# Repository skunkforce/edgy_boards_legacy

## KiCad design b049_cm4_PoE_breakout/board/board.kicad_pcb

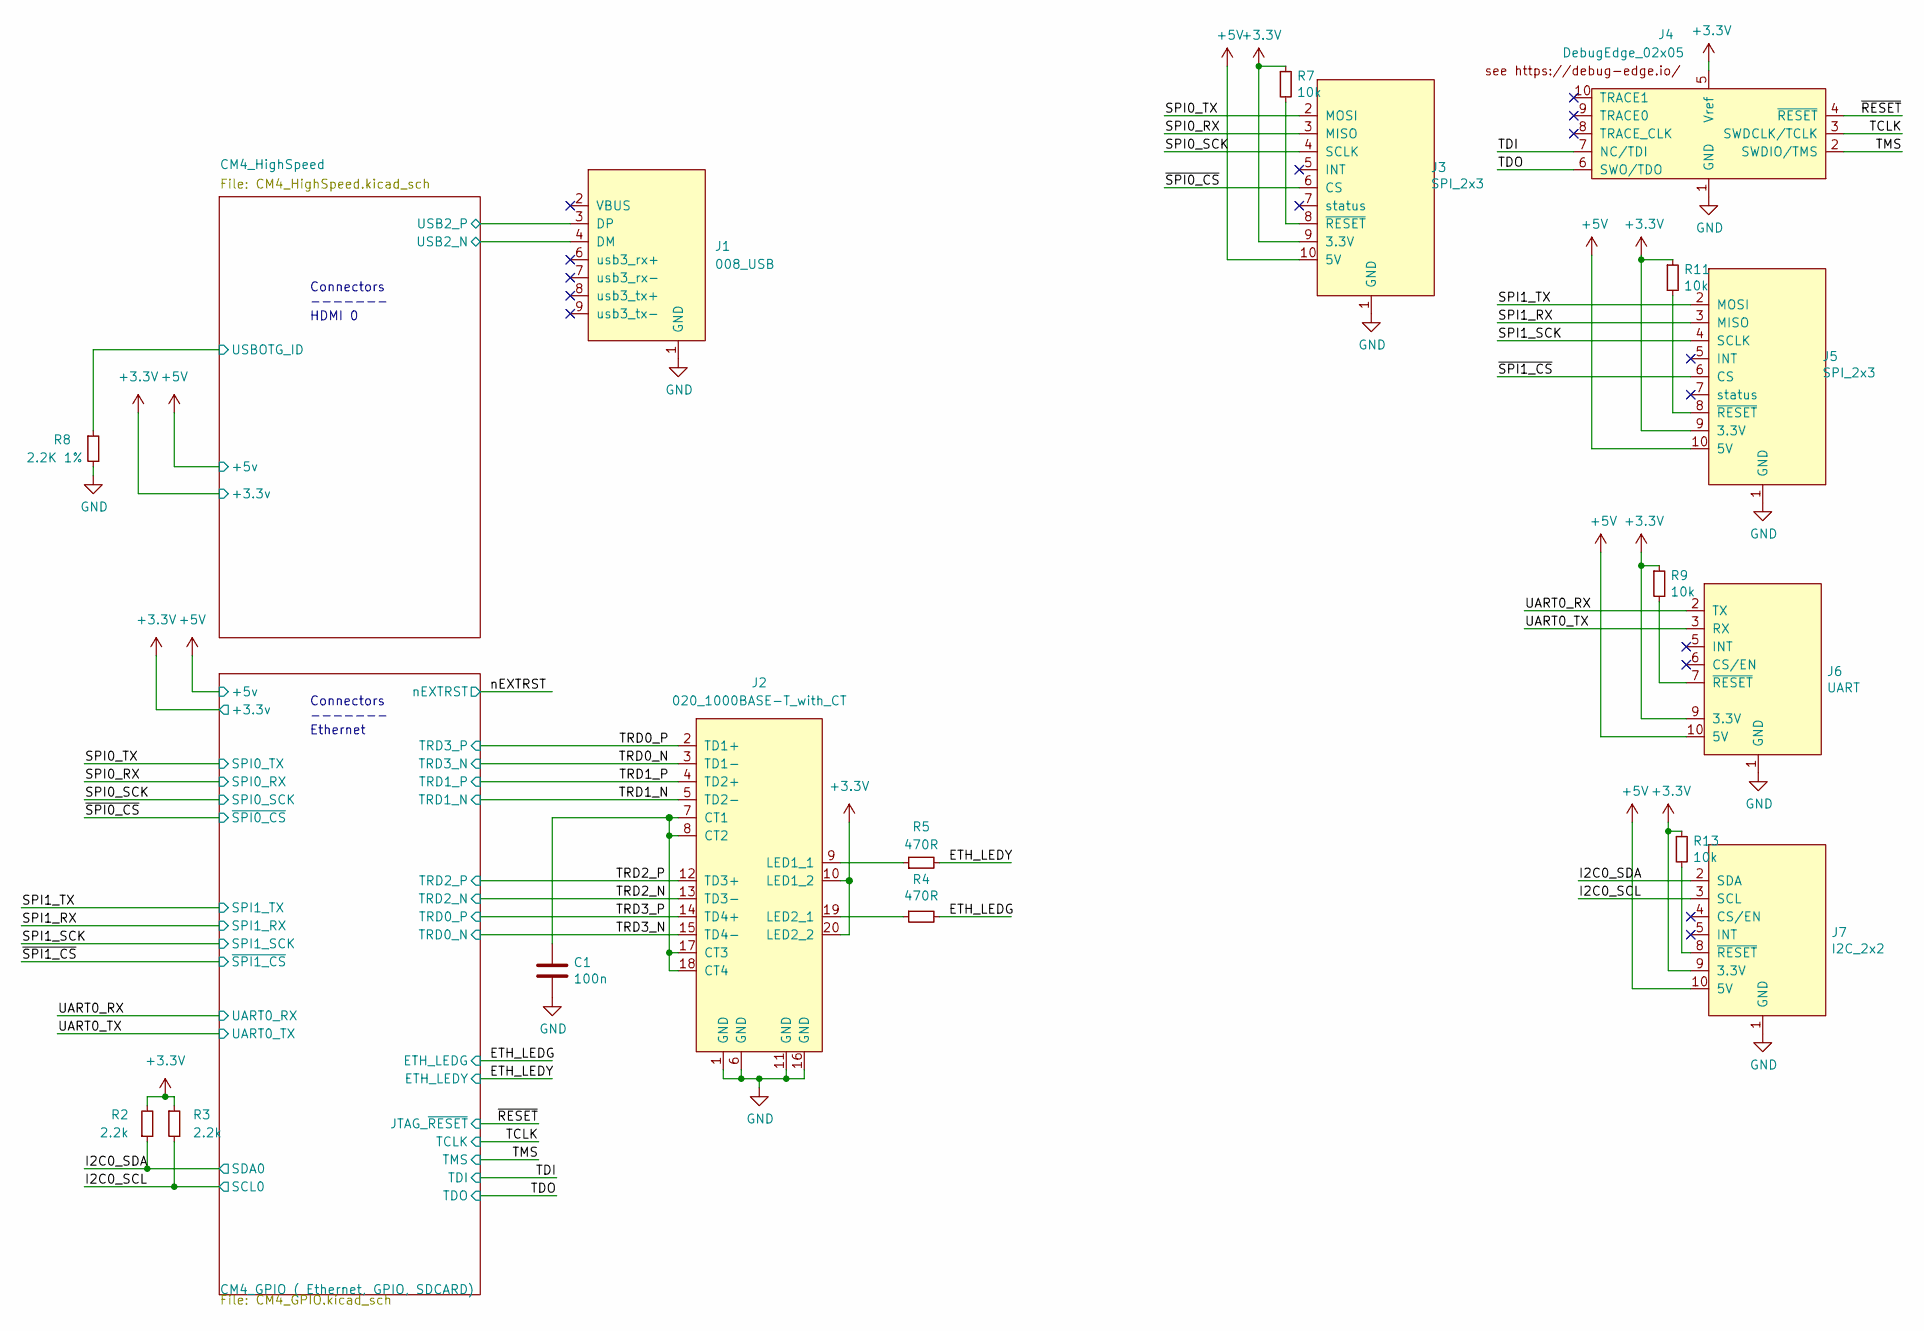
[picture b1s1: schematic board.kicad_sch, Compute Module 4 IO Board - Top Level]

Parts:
C1: 100n; C_0402_1005Metric; Part Description 0.1uF 10% 16V Ceramic Capacitor X7R 040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
J1: 008_USB; on_edge_2x05_host
J2: 020_1000BASE-T_with_CT; on_edge_2x10_host
J3: SPI_2x3; on_edge_2x05_up_host
J4: DebugEdge_02x05; debug_edge_2x05_host
J5: SPI_2x3; on_edge_2x05_host
J6: UART; on_edge_2x05_host
J7: I2C_2x2; on_edge_2x05_host
R2, R3: 2.2k; R_0603_1608Metric
R4, R5: 470R; R_0402_1005Metric; Part Description Resistor 470R M1005 1% 63mW
R7, R9, R11, R13: 10k; R_0603_1608Metric
R8: 2.2K 1%; R_0402_1005Metric; Part Description Resistor 2.2K M1005 1% 63mW

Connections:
+3V3: J2.10 (LED1_2), J2.20 (LED2_2), J3.9 (3.3V), J4.5 (Vref), J5.9 (3.3V), J6.9 (3.3V), J7.9 (3.3V), R2.2, R3.1, R7.1, R9.1, R11.1, R13.1; also elsewhere on the board
+5V: J3.10 (5V), J5.10 (5V), J6.10 (5V), J7.10 (5V); also elsewhere on the board
/CM4_HighSpeed/USB2_N: J1.4 (DM); also elsewhere on the board
/CM4_HighSpeed/USB2_P: J1.3 (DP); also elsewhere on the board
/CM4_HighSpeed/USBOTG_ID: R8.1; also elsewhere on the board
/ETH_LEDG: R4.2; also elsewhere on the board
/ETH_LEDY: R5.2; also elsewhere on the board
/I2C0_SCL: J7.3 (SCL), R3.2; also elsewhere on the board
/I2C0_SDA: J7.2 (SDA), R2.1; also elsewhere on the board
/SPI0_RX: J3.3 (MISO); also elsewhere on the board
/SPI0_SCK: J3.4 (SCLK); also elsewhere on the board
/SPI0_TX: J3.2 (MOSI); also elsewhere on the board
/SPI1_RX: J5.3 (MISO); also elsewhere on the board
/SPI1_SCK: J5.4 (SCLK); also elsewhere on the board
/SPI1_TX: J5.2 (MOSI); also elsewhere on the board
/TCLK: J4.3 (SWDCLK/TCLK); also elsewhere on the board
/TDI: J4.7 (NC/TDI); also elsewhere on the board
/TDO: J4.6 (SWO/TDO); also elsewhere on the board
/TMS: J4.2 (SWDIO/TMS); also elsewhere on the board
/TRD0_N: J2.3 (TD1-); also elsewhere on the board
/TRD0_P: J2.2 (TD1+); also elsewhere on the board
/TRD1_N: J2.5 (TD2-); also elsewhere on the board
/TRD1_P: J2.4 (TD2+); also elsewhere on the board
/TRD2_N: J2.13 (TD3-); also elsewhere on the board
/TRD2_P: J2.12 (TD3+); also elsewhere on the board
/TRD3_N: J2.15 (TD4-); also elsewhere on the board
/TRD3_P: J2.14 (TD4+); also elsewhere on the board
/UART0_RX: J6.2 (TX); also elsewhere on the board
/UART0_TX: J6.3 (RX); also elsewhere on the board
/~RESET: J4.4 (~RESET); also elsewhere on the board
/~SPI0_CS: J3.6 (CS); also elsewhere on the board
/~SPI1_CS: J5.6 (CS); also elsewhere on the board
GND: C1.2, J1.1 (GND), J2.1 (GND), J2.6 (GND), J2.11 (GND), J2.16 (GND), J3.1 (GND), J4.1 (GND), J5.1 (GND), J6.1 (GND), J7.1 (GND), R8.2; also elsewhere on the board
unnamed: C1.1, J2.7 (CT1), J2.8 (CT2), J2.17 (CT3), J2.18 (CT4)
unnamed: J2.9 (LED1_1), R5.1
unnamed: J2.19 (LED2_1), R4.1
unnamed: J3.8 (~RESET), R7.2
unnamed: J5.8 (~RESET), R11.2
unnamed: J6.7 (~RESET), R9.2
unnamed: J7.8 (~RESET), R13.2

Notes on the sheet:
Connectors ------- Ethernet
Connectors ------- HDMI 0

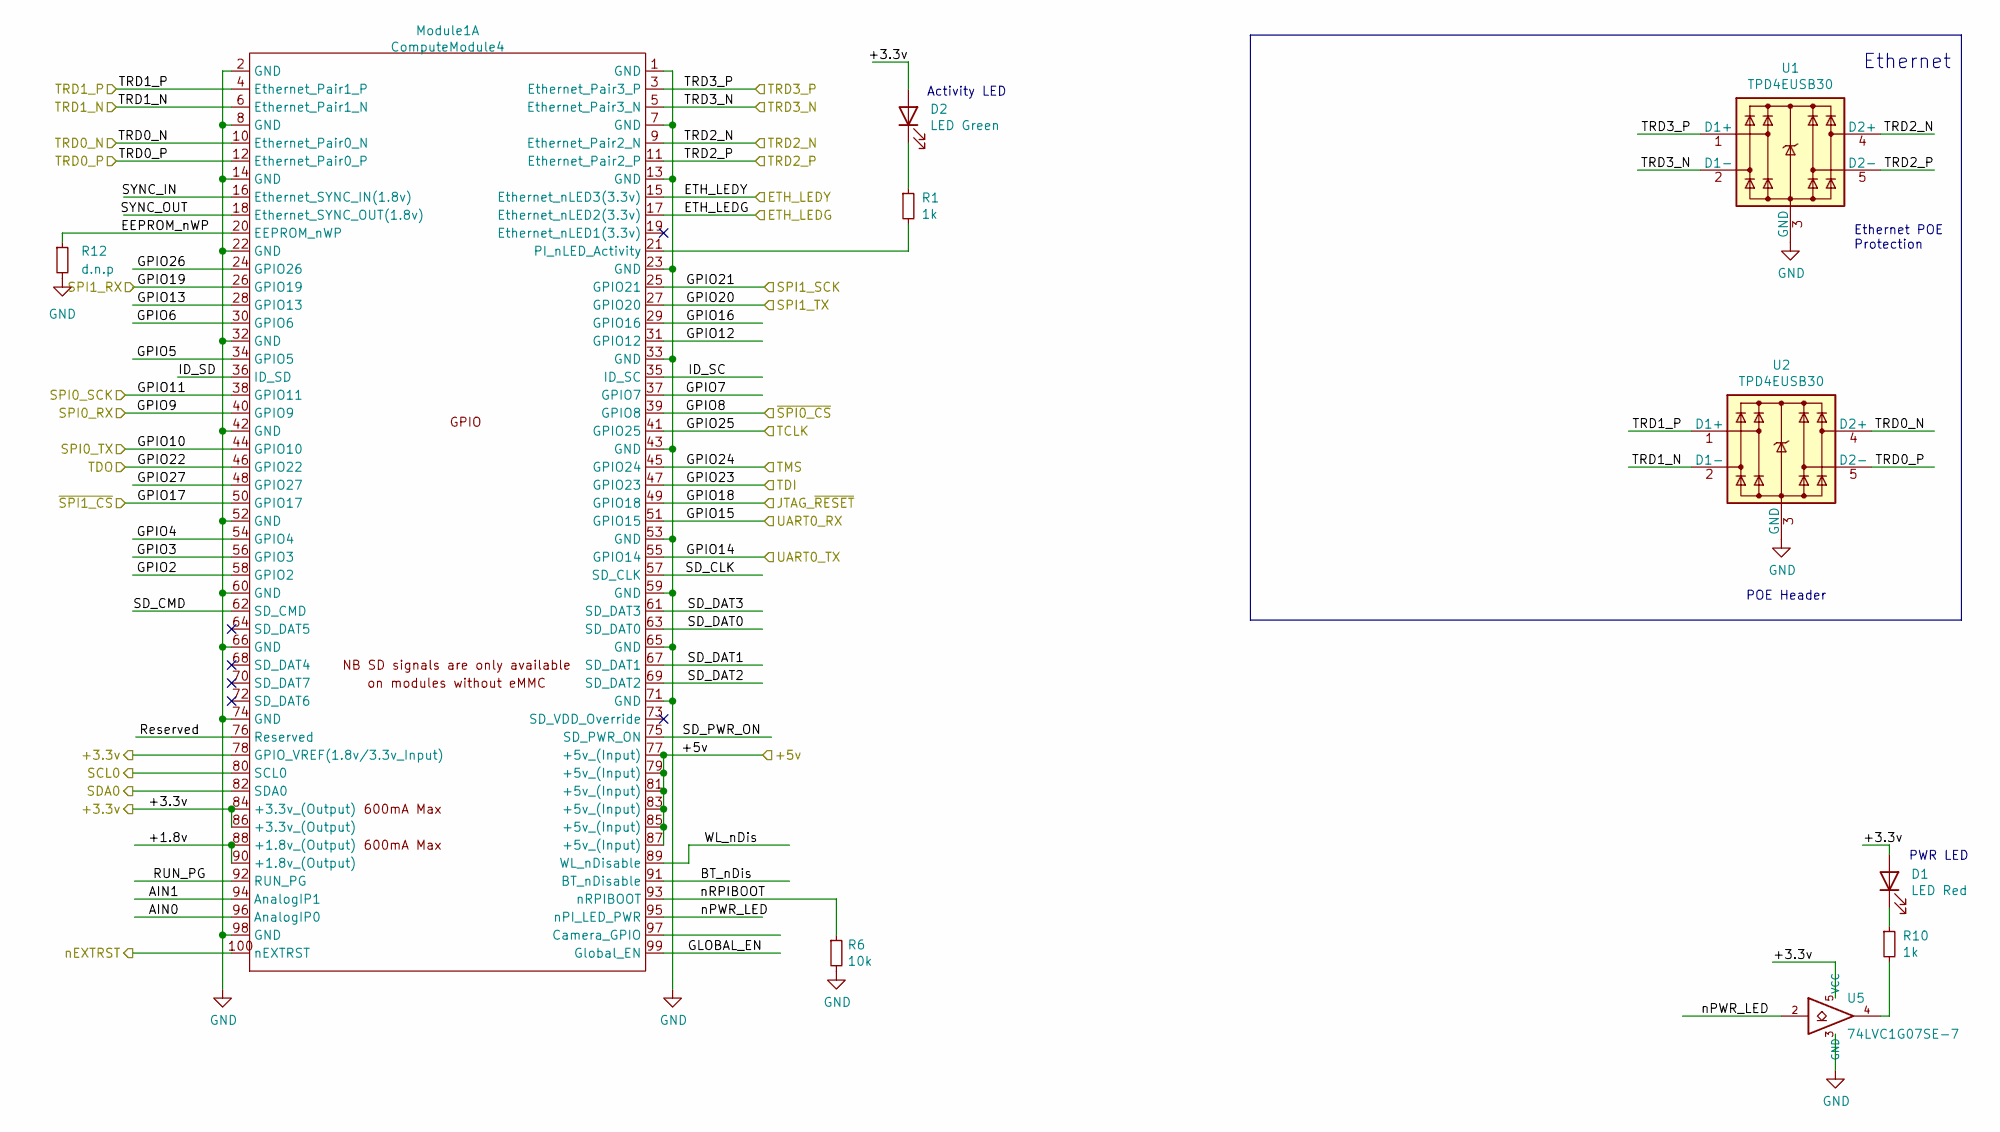
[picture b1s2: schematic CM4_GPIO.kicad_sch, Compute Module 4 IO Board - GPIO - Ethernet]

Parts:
D1: LED Red; LED_0603_1608Metric; Part Description Red 620nm LED Indication - Discrete 2.2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
D2: LED Green; LED_0603_1608Metric; Part Description Green 572nm LED Indication - Discrete 2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
Module1: ComputeModule4; Raspberry-Pi-4-Compute-Module; Part Description 100 Position Connector Receptacle, Cent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
R1, R10: 1k; R_0402_1005Metric; Part Description Resistor 1K M1005 1% 63mW
R6: 10k; R_0603_1608Metric
R12: d.n.p; R_0603_1608Metric
U1, U2: TPD4EUSB30; USON-10_2.5x1.0mm_P0.5mm; Part Description Quad TVS diode for high speed signals (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
U5: 74LVC1G07SE-7; SOT-353_SC-70-5; Part Description Buffer, Non-Inverting 1 Element 1 Bit p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

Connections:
+3V3: D1.2 (A), D2.2 (A), Module1.78 (GPIO_VREF(1.8v/3.3v_Input)), Module1.84 (+3.3v_(Output)), Module1.86 (+3.3v_(Output)), U5.5 (VCC); also elsewhere on the board
+5V: Module1.77 (+5v_(Input)), Module1.79 (+5v_(Input)), Module1.81 (+5v_(Input)), Module1.83 (+5v_(Input)), Module1.85 (+5v_(Input)), Module1.87 (+5v_(Input)); also elsewhere on the board
/CM4_GPIO ( Ethernet, GPIO, SDCARD)/+1.8v: Module1.88 (+1.8v_(Output)), Module1.90 (+1.8v_(Output))
/CM4_GPIO ( Ethernet, GPIO, SDCARD)/AIN0: Module1.96 (AnalogIP0)
/CM4_GPIO ( Ethernet, GPIO, SDCARD)/AIN1: Module1.94 (AnalogIP1)
/CM4_GPIO ( Ethernet, GPIO, SDCARD)/BT_nDis: Module1.91 (BT_nDisable)
/CM4_GPIO ( Ethernet, GPIO, SDCARD)/EEPROM_nWP: Module1.20 (EEPROM_nWP), R12.1
/CM4_GPIO ( Ethernet, GPIO, SDCARD)/GLOBAL_EN: Module1.99 (Global_EN)
/CM4_GPIO ( Ethernet, GPIO, SDCARD)/GPIO2: Module1.58 (GPIO2)
/CM4_GPIO ( Ethernet, GPIO, SDCARD)/GPIO3: Module1.56 (GPIO3)
/CM4_GPIO ( Ethernet, GPIO, SDCARD)/GPIO4: Module1.54 (GPIO4)
/CM4_GPIO ( Ethernet, GPIO, SDCARD)/GPIO5: Module1.34 (GPIO5)
/CM4_GPIO ( Ethernet, GPIO, SDCARD)/GPIO6: Module1.30 (GPIO6)
/CM4_GPIO ( Ethernet, GPIO, SDCARD)/GPIO7: Module1.37 (GPIO7)
/CM4_GPIO ( Ethernet, GPIO, SDCARD)/GPIO12: Module1.31 (GPIO12)
/CM4_GPIO ( Ethernet, GPIO, SDCARD)/GPIO13: Module1.28 (GPIO13)
/CM4_GPIO ( Ethernet, GPIO, SDCARD)/GPIO16: Module1.29 (GPIO16)
/CM4_GPIO ( Ethernet, GPIO, SDCARD)/GPIO26: Module1.24 (GPIO26)
/CM4_GPIO ( Ethernet, GPIO, SDCARD)/GPIO27: Module1.48 (GPIO27)
/CM4_GPIO ( Ethernet, GPIO, SDCARD)/ID_SC: Module1.35 (ID_SC)
/CM4_GPIO ( Ethernet, GPIO, SDCARD)/ID_SD: Module1.36 (ID_SD)
/CM4_GPIO ( Ethernet, GPIO, SDCARD)/RUN_PG: Module1.92 (RUN_PG)
/CM4_GPIO ( Ethernet, GPIO, SDCARD)/Reserved: Module1.76 (Reserved)
/CM4_GPIO ( Ethernet, GPIO, SDCARD)/SD_CLK: Module1.57 (SD_CLK)
/CM4_GPIO ( Ethernet, GPIO, SDCARD)/SD_CMD: Module1.62 (SD_CMD)
/CM4_GPIO ( Ethernet, GPIO, SDCARD)/SD_DAT0: Module1.63 (SD_DAT0)
/CM4_GPIO ( Ethernet, GPIO, SDCARD)/SD_DAT1: Module1.67 (SD_DAT1)
/CM4_GPIO ( Ethernet, GPIO, SDCARD)/SD_DAT2: Module1.69 (SD_DAT2)
/CM4_GPIO ( Ethernet, GPIO, SDCARD)/SD_DAT3: Module1.61 (SD_DAT3)
/CM4_GPIO ( Ethernet, GPIO, SDCARD)/SD_PWR_ON: Module1.75 (SD_PWR_ON)
/CM4_GPIO ( Ethernet, GPIO, SDCARD)/SYNC_IN: Module1.16 (Ethernet_SYNC_IN(1.8v))
/CM4_GPIO ( Ethernet, GPIO, SDCARD)/SYNC_OUT: Module1.18 (Ethernet_SYNC_OUT(1.8v))
/CM4_GPIO ( Ethernet, GPIO, SDCARD)/WL_nDis: Module1.89 (WL_nDisable)
/CM4_GPIO ( Ethernet, GPIO, SDCARD)/nPWR_LED: Module1.95 (nPI_LED_PWR), U5.2
/CM4_GPIO ( Ethernet, GPIO, SDCARD)/nRPIBOOT: Module1.93 (nRPIBOOT), R6.1
/ETH_LEDG: Module1.17 (Ethernet_nLED2(3.3v)); also elsewhere on the board
/ETH_LEDY: Module1.15 (Ethernet_nLED3(3.3v)); also elsewhere on the board
/I2C0_SCL: Module1.80 (SCL0); also elsewhere on the board
/I2C0_SDA: Module1.82 (SDA0); also elsewhere on the board
/SPI0_RX: Module1.40 (GPIO9); also elsewhere on the board
/SPI0_SCK: Module1.38 (GPIO11); also elsewhere on the board
/SPI0_TX: Module1.44 (GPIO10); also elsewhere on the board
/SPI1_RX: Module1.26 (GPIO19); also elsewhere on the board
/SPI1_SCK: Module1.25 (GPIO21); also elsewhere on the board
/SPI1_TX: Module1.27 (GPIO20); also elsewhere on the board
/TCLK: Module1.41 (GPIO25); also elsewhere on the board
/TDI: Module1.47 (GPIO23); also elsewhere on the board
/TDO: Module1.46 (GPIO22); also elsewhere on the board
/TMS: Module1.45 (GPIO24); also elsewhere on the board
/TRD0_N: Module1.5 (Ethernet_Pair3_N), U1.2 (D1-), U1.9; also elsewhere on the board
/TRD0_P: Module1.3 (Ethernet_Pair3_P), U1.1 (D1+), U1.10; also elsewhere on the board
/TRD1_N: Module1.6 (Ethernet_Pair1_N), U2.2 (D1-), U2.9; also elsewhere on the board
/TRD1_P: Module1.4 (Ethernet_Pair1_P), U2.1 (D1+), U2.10; also elsewhere on the board
/TRD2_N: Module1.9 (Ethernet_Pair2_N), U1.4 (D2+), U1.7; also elsewhere on the board
/TRD2_P: Module1.11 (Ethernet_Pair2_P), U1.5 (D2-), U1.6; also elsewhere on the board
/TRD3_N: Module1.10 (Ethernet_Pair0_N), U2.4 (D2+), U2.7; also elsewhere on the board
/TRD3_P: Module1.12 (Ethernet_Pair0_P), U2.5 (D2-), U2.6; also elsewhere on the board
/UART0_RX: Module1.51 (GPIO15); also elsewhere on the board
/UART0_TX: Module1.55 (GPIO14); also elsewhere on the board
/nEXTRST: Module1.100 (nEXTRST)
/~RESET: Module1.49 (GPIO18); also elsewhere on the board
/~SPI0_CS: Module1.39 (GPIO8); also elsewhere on the board
/~SPI1_CS: Module1.50 (GPIO17); also elsewhere on the board
GND: Module1.1 (GND), Module1.2 (GND), Module1.7 (GND), Module1.8 (GND), Module1.13 (GND), Module1.14 (GND), Module1.22 (GND), Module1.23 (GND), Module1.32 (GND), Module1.33 (GND), Module1.42 (GND), Module1.43 (GND), Module1.52 (GND), Module1.53 (GND), Module1.59 (GND), Module1.60 (GND), Module1.65 (GND), Module1.66 (GND), Module1.71 (GND), Module1.74 (GND), Module1.98 (GND), R6.2, R12.2, U1.3 (GND), U1.8 (GND), U2.3 (GND), U2.8 (GND), U5.3 (GND); also elsewhere on the board
unnamed: D1.1 (K), R10.1
unnamed: D2.1 (K), R1.1
unnamed: Module1.21 (PI_nLED_Activity), R1.2
unnamed: R10.2, U5.4

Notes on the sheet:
PWR LED
Ethernet POE Protection
Ethernet
Activity LED
POE Header

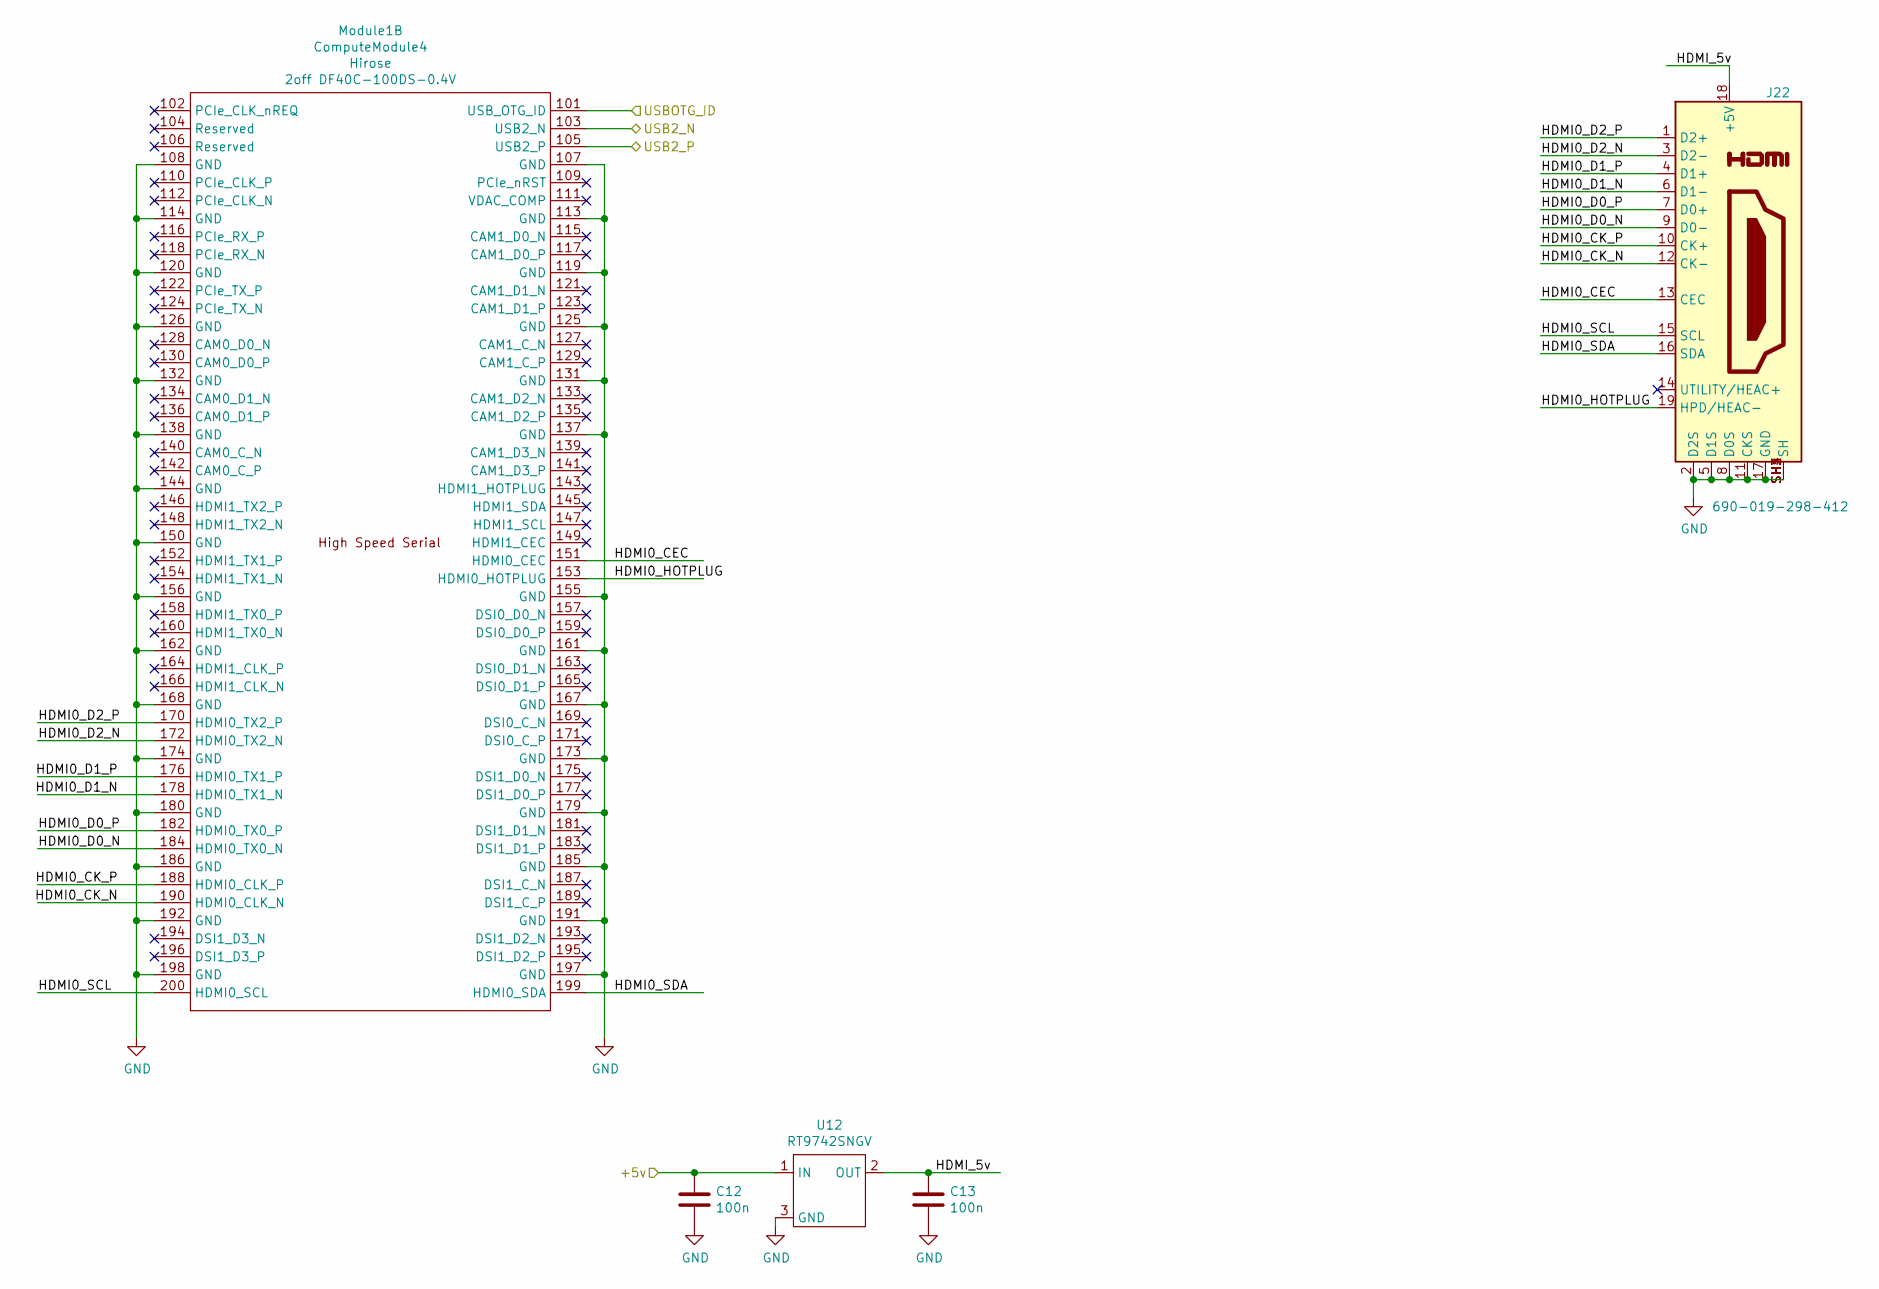
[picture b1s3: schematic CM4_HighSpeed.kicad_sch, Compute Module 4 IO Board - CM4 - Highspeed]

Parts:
C12, C13: 100n; C_0402_1005Metric; Part Description 0.1uF 10% 16V Ceramic Capacitor X7R 040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
J22: 690-019-298-412; EDAC 690-019-298-412; Part Description HDMI Connector, Right Angle, 19 Contact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
Module1: ComputeModule4; Raspberry-Pi-4-Compute-Module; Part Description 100 Position Connector Receptacle, Cent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
U12: RT9742SNGV; SOT-23; Part Description Power Switch/Driver 1:1 N-Channel 500mA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

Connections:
+5V: C12.1, U12.1 (IN); also elsewhere on the board
/CM4_HighSpeed/HDMI0_CEC: J22.13 (CEC), Module1.151 (HDMI0_CEC)
/CM4_HighSpeed/HDMI0_CK_N: J22.12 (CK-), Module1.190 (HDMI0_CLK_N)
/CM4_HighSpeed/HDMI0_CK_P: J22.10 (CK+), Module1.188 (HDMI0_CLK_P)
/CM4_HighSpeed/HDMI0_D0_N: J22.9 (D0-), Module1.184 (HDMI0_TX0_N)
/CM4_HighSpeed/HDMI0_D0_P: J22.7 (D0+), Module1.182 (HDMI0_TX0_P)
/CM4_HighSpeed/HDMI0_D1_N: J22.6 (D1-), Module1.178 (HDMI0_TX1_N)
/CM4_HighSpeed/HDMI0_D1_P: J22.4 (D1+), Module1.176 (HDMI0_TX1_P)
/CM4_HighSpeed/HDMI0_D2_N: J22.3 (D2-), Module1.172 (HDMI0_TX2_N)
/CM4_HighSpeed/HDMI0_D2_P: J22.1 (D2+), Module1.170 (HDMI0_TX2_P)
/CM4_HighSpeed/HDMI0_HOTPLUG: J22.19 (HPD/HEAC-), Module1.153 (HDMI0_HOTPLUG)
/CM4_HighSpeed/HDMI0_SCL: J22.15 (SCL), Module1.200 (HDMI0_SCL)
/CM4_HighSpeed/HDMI0_SDA: J22.16 (SDA), Module1.199 (HDMI0_SDA)
/CM4_HighSpeed/HDMI_5v: C13.1, J22.18 (+5V), U12.2 (OUT)
/CM4_HighSpeed/USB2_N: Module1.103 (USB2_N); also elsewhere on the board
/CM4_HighSpeed/USB2_P: Module1.105 (USB2_P); also elsewhere on the board
/CM4_HighSpeed/USBOTG_ID: Module1.101 (USB_OTG_ID); also elsewhere on the board
GND: C12.2, C13.2, J22.2 (D2S), J22.5 (D1S), J22.8 (D0S), J22.11 (CKS), J22.17 (GND), J22.SH1 (SH), J22.SH2 (SH), J22.SH3 (SH), J22.SH4 (SH), Module1.107 (GND), Module1.108 (GND), Module1.113 (GND), Module1.114 (GND), Module1.119 (GND), Module1.120 (GND), Module1.125 (GND), Module1.126 (GND), Module1.131 (GND), Module1.132 (GND), Module1.137 (GND), Module1.138 (GND), Module1.144 (GND), Module1.150 (GND), Module1.155 (GND), Module1.156 (GND), Module1.161 (GND), Module1.162 (GND), Module1.167 (GND), Module1.168 (GND), Module1.173 (GND), Module1.174 (GND), Module1.179 (GND), Module1.180 (GND), Module1.185 (GND), Module1.186 (GND), Module1.191 (GND), Module1.192 (GND), Module1.197 (GND), Module1.198 (GND), U12.3 (GND); also elsewhere on the board

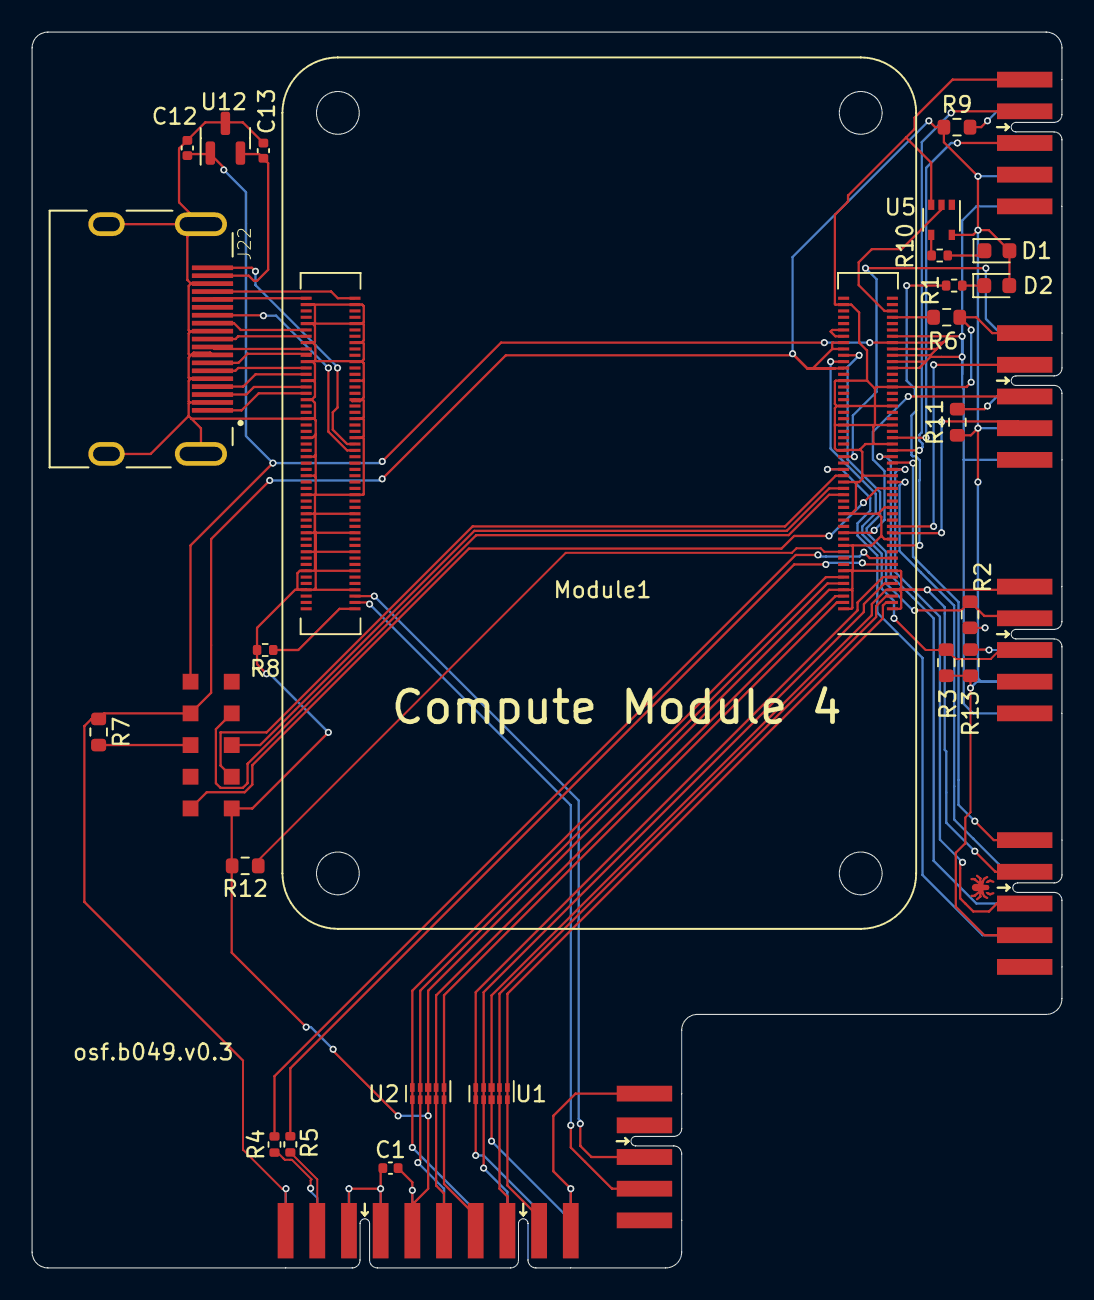
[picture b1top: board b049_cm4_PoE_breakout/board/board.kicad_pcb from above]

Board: 4 copper layers, 65.0 x 78.0 mm, 31 parts (0 on the bottom side), 61 nets.

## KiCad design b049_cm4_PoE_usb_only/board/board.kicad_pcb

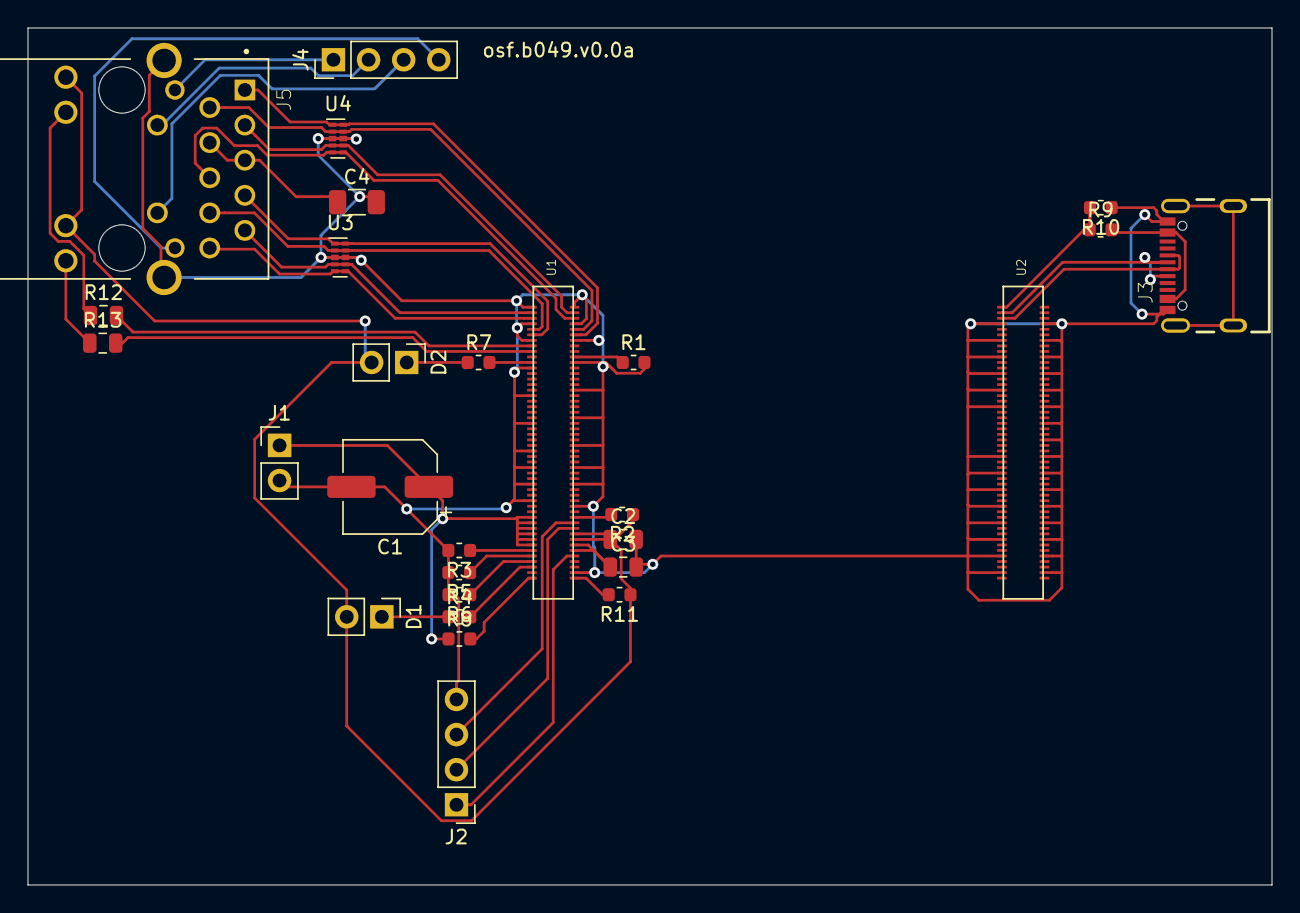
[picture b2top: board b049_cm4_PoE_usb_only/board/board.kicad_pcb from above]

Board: 2 copper layers, 90.0 x 62.0 mm, 28 parts (0 on the bottom side), 40 nets.

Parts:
C1: 100uF; CP_Elec_6.3x5.9
C2, C3: 1uF; C_0805_2012Metric
C4: C_Small; C_1206_3216Metric
D1, D2: LED; PinHeader_1x02_P2.54mm_Vertical
J1: Conn_01x02_Male; PinHeader_1x02_P2.54mm_Vertical
J2, J4: Conn_01x04_Male; PinHeader_1x04_P2.54mm_Vertical
J3: USB4105-GF-A; GCT_USB4105-GF-A
J5: A70-112-331N126; EDAC_A70-112-331N126
R1, R2, R3, R4, R5, R6, R7, R8, R11: 1k; R_0603_1608Metric
R9, R10: 2.2k; R_0603_1608Metric
R12, R13: 470R; R_0805_2012Metric
U1: piCM4_A; HRS_DF40C-100DS-0.4V(51)
U2: piCM4_B; HRS_DF40C-100DS-0.4V(51)
U3, U4: TPD4EUSB30; USON-10_2.5x1.0mm_P0.5mm_connect_through

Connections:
/3.3v: C2.1, D1.2, D2.2, J5.15, J5.17, R2.1, R11.1, U1.84, U1.86
/Ethernet/E_P0+: J5.1, U1.12, U4.1
/Ethernet/E_P0-: J5.2, U1.10, U4.2
/Ethernet/E_P1+: J5.3, U1.4, U4.4
/Ethernet/E_P1-: J5.6, U1.6, U4.5
/Ethernet/E_P2+: J5.7, U1.11, U3.1
/Ethernet/E_P2-: J5.8, U1.9, U3.2
/Ethernet/E_P3+: J5.9, U1.3, U3.4
/Ethernet/E_P3-: J5.10, U1.5, U3.5
/cm/5v: C1.1, J1.1, R8.1, U1.77, U1.79, U1.81, U1.83, U1.85, U1.87
/cm/BT_Disable: R5.1, U1.91
/cm/EEPROM_~WP: R1.1, U1.20
/cm/EXTRST: R11.2, U1.100
/cm/E_LED2: R13.2, U1.17
/cm/E_LED3: R12.2, U1.15
/cm/GLOBAL_EN: R8.2, U1.99
/cm/GPIO_VREF: R2.2, U1.78
/cm/PI_LED_Activity: R7.2, U1.21
/cm/PI_LED_PWR: R4.2, U1.95
/cm/RPIBOOT: R6.1, U1.93
/cm/RUN_PG: J2.1, U1.92
/cm/SCL0: J2.3, U1.80
/cm/SDA0: J2.2, U1.82
/cm/USB+: J3.A6, J3.B6, U2.5
/cm/USB-: J3.A7, J3.B7, U2.3
/cm/USBOTG_ID: R9.1, R10.2, U2.1
/cm/WL_Disable: R3.1, U1.89
GND: C1.2, C2.2, C3.2, C4.2, J1.2, J2.4, J3.A1/B12, J3.B1/A12, J5.S1, J5.S2, R1.2, R3.2, R5.2, R6.2, R10.1, U1.1, U1.2, U1.7, U1.8, U1.13, U1.14, U1.22, U1.23, U1.32, U1.33, U1.42, U1.43, U1.52, U1.53, U1.59, U1.60, U1.65, U1.66, U1.71, U1.74, U1.98, U2.7, U2.8, U2.13, U2.14, U2.19, U2.20, U2.25, U2.26, U2.31, U2.32, U2.37, U2.38, U2.44, U2.50, U2.55, U2.56, U2.61, U2.62, U2.67, U2.68, U2.73, U2.74, U2.79, U2.80, U2.85, U2.86, U2.91, U2.92, U2.97, U2.98, U3.3, U4.3
unnamed: C3.1, U1.88, U1.90
unnamed: C4.1, J5.4, J5.5
unnamed: D1.1, R4.1
unnamed: D2.1, R7.1
unnamed: J3.A4/B9, J3.B4/A9, R9.2
unnamed: J3.G1, J3.G2, J3.G3, J3.G4
unnamed: J4.1, J5.11
unnamed: J4.2, J5.12
unnamed: J4.3, J5.13
unnamed: J4.4, J5.14
unnamed: J5.16, R12.1
unnamed: J5.18, R13.1

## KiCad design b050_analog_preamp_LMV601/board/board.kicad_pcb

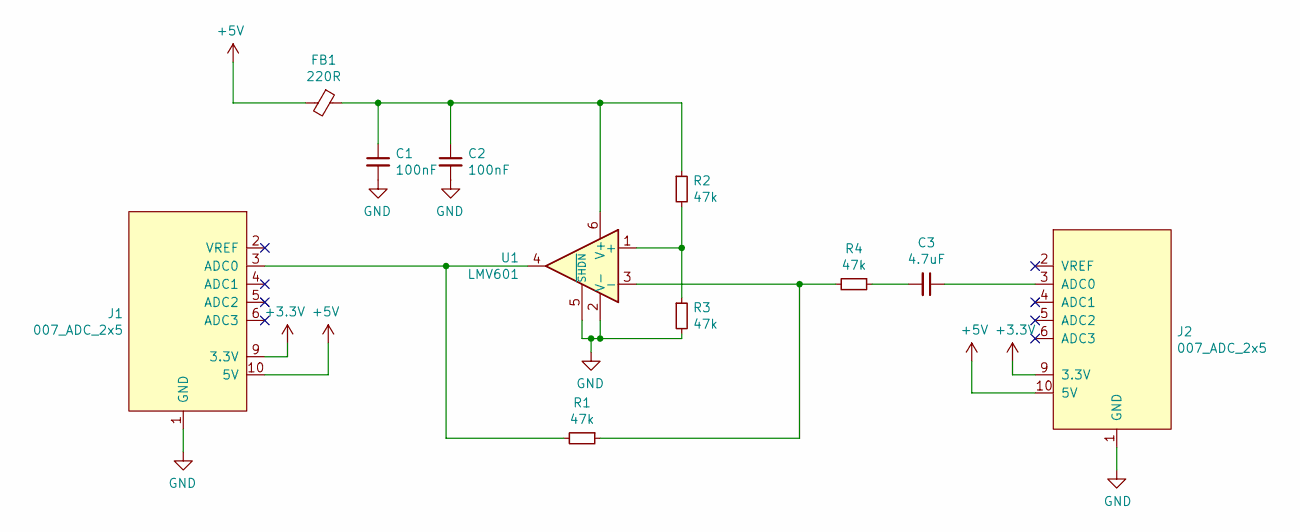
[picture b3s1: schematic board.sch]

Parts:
C1, C2: 100nF; C_0603_1608Metric
C3: 4.7uF; C_0805_2012Metric
FB1: 220R; C_0805_2012Metric
J1: 007_ADC_2x5; on_edge_2x05_device
J2: 007_ADC_2x5; on_edge_2x05_host
R1, R2, R3, R4: 47k; R_0603_1608Metric
U1: LMV601; SOT-363_SC-70-6

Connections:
+3V3: J1.9 (3.3V), J2.9 (3.3V)
+5V: FB1.2, J1.10 (5V), J2.10 (5V)
GND: C1.2, C2.2, J1.1 (GND), J2.1 (GND), R3.2, U1.2 (V-), U1.5 (~SHDN)
unnamed: C1.1, C2.1, FB1.1, R2.1, U1.6 (V+)
unnamed: C3.1, J2.3 (ADC0)
unnamed: C3.2, R4.1
unnamed: J1.3 (ADC0), R1.2, U1.4
unnamed: R1.1, R4.2, U1.3 (-)
unnamed: R2.2, R3.1, U1.1 (+)

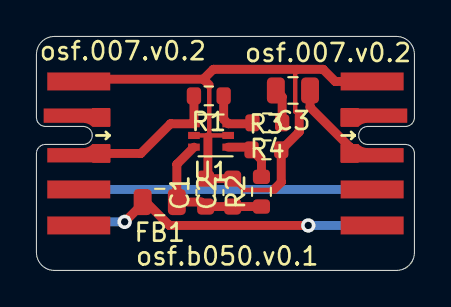
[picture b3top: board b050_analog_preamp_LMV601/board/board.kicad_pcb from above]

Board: 2 copper layers, 21.0 x 13.0 mm, 11 parts (0 on the bottom side), 9 nets.

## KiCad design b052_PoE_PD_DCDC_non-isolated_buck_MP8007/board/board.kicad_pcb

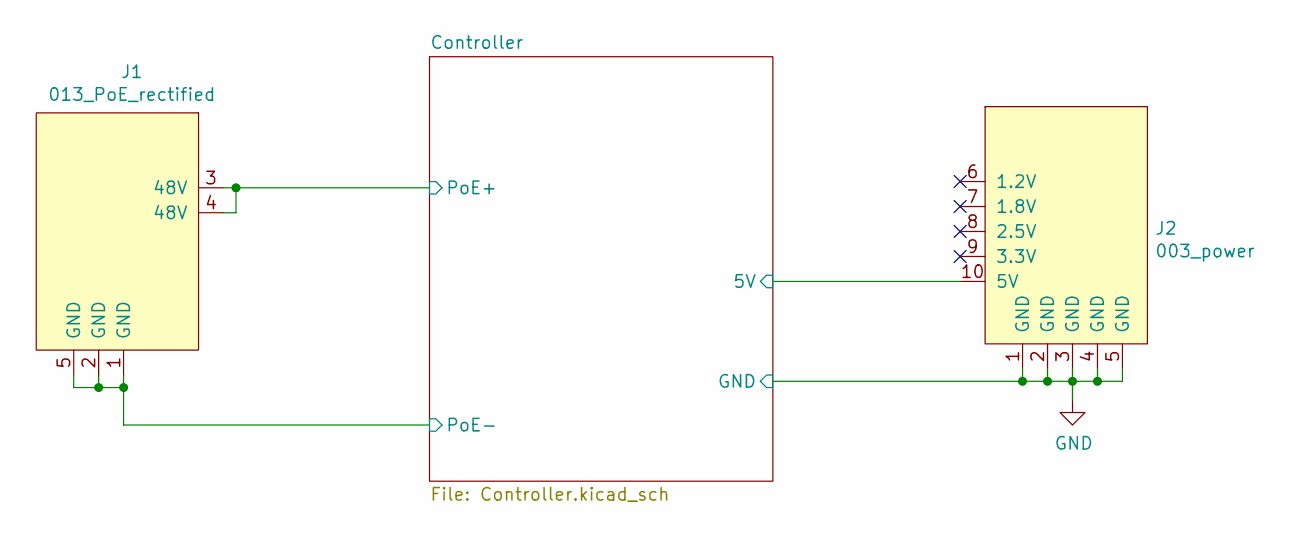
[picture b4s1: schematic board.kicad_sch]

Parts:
J1: 013_PoE_rectified; on_edge_2x05_device
J2: 003_power; on_edge_2x05_host

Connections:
/Controller/5V: J1.3 (48V), J1.4 (48V), J2.10 (5V); also elsewhere on the board
/Controller/PoE-: J1.1 (GND), J1.2 (GND), J1.5 (GND); also elsewhere on the board
GND: J2.1 (GND), J2.2 (GND), J2.3 (GND), J2.4 (GND), J2.5 (GND); also elsewhere on the board

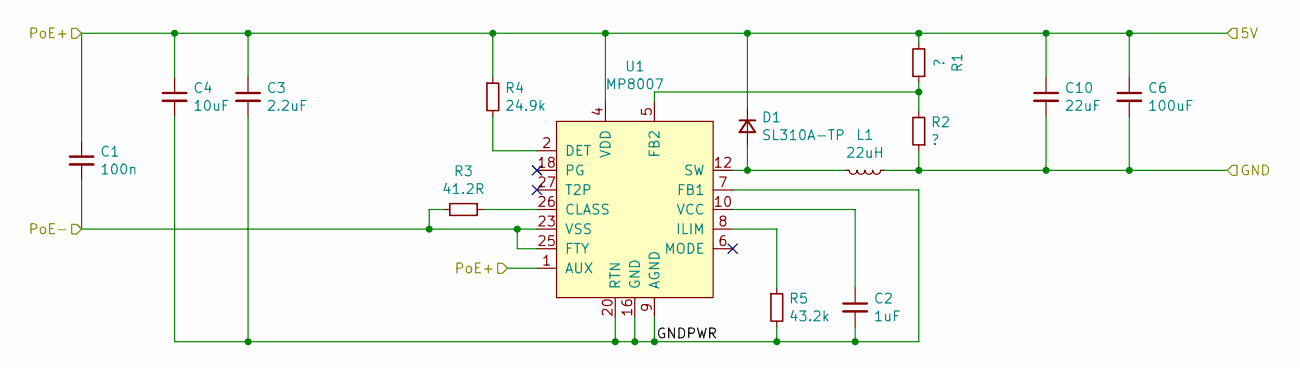
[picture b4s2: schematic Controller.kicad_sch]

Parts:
C1: 100n; C_0603_1608Metric
C2: 1uF; C_0603_1608Metric
C3: 2.2uF; C_1210_3225Metric
C4: 10uF; C_1210_3225Metric
C6: 100uF; C_1206_3216Metric
C10: 22uF; C_1206_3216Metric
D1: SL310A-TP; D_SMA
L1: 22uH; L_2512_6332Metric
R1, R2: ?; R_0603_1608Metric
R3: 41.2R; R_0603_1608Metric
R4: 24.9k; R_0603_1608Metric
R5: 43.2k; R_0603_1608Metric
U1: MP8007; QFN-28-1EP_4x5mm_P0.5mm_EP2.65x3.65mm_ThermalVias

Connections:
/Controller/5V: C1.1, C3.1, C4.1, C6.1, C10.1, D1.1 (K), R1.2, R4.1, U1.1 (AUX), U1.4 (VDD); also elsewhere on the board
/Controller/GNDPWR: C2.2, C3.2, C4.2, R5.2, U1.6 (MODE), U1.7 (FB1), U1.9 (AGND), U1.14 (NC), U1.15 (NC), U1.16 (GND), U1.17, U1.19 (NC), U1.20 (RTN), U1.21, U1.22 (NC), U1.29 (GND)
/Controller/PoE-: C1.2, R3.2, U1.23 (VSS), U1.24, U1.25 (FTY); also elsewhere on the board
GND: C6.2, C10.2, L1.1, R2.1; also elsewhere on the board
unnamed: C2.1, U1.10 (VCC)
unnamed: D1.2 (A), L1.2, U1.12 (SW), U1.13
unnamed: R1.1, R2.2, U1.5 (FB2)
unnamed: R3.1, U1.26 (CLASS)
unnamed: R4.2, U1.2 (DET)
unnamed: R5.1, U1.8 (ILIM)

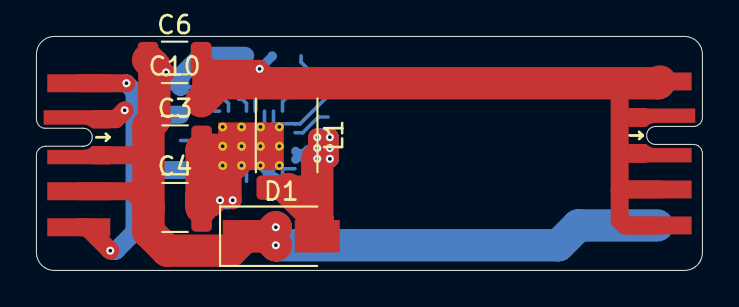
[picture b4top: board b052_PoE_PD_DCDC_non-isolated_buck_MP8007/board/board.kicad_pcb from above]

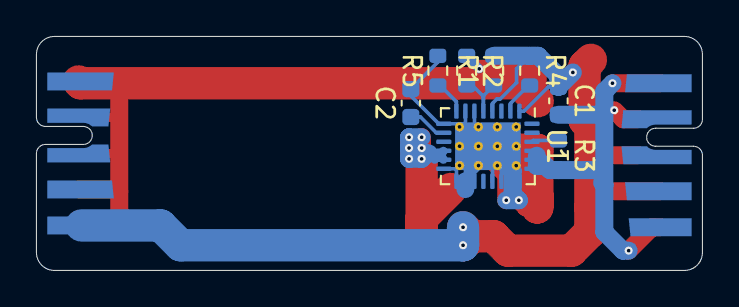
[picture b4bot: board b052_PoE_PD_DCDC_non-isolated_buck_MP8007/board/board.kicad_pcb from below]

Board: 2 copper layers, 37.0 x 13.0 mm, 16 parts (8 on the bottom side), 10 nets.

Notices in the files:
b049_cm4_PoE_breakout/board/CM4_GPIO.kicad_sch:
© 2020-2022 Raspberry Pi Ltd (formerly Raspberry Pi (Trading) Ltd.)
